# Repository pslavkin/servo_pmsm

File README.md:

# PMSM Servo motor driver based on C2000 - PCB

> development of a customized high precision microcontrolled permament magnet embedded servo motor

## Progress
<!--- 
- 
- 
- 
- 
embedded gist

https://gist.github.com/rxaviers/7360908

- :heavy_check_mark: connected to a chinise CNC works!
- :red_circle:       Dual core interconnect IPC
-->
- :heavy_check_mark:    controller schematics from Altium to kicad
- :heavy_check_mark:    setting kicad libs, datasheet, remove unused IC's
- :heavy_check_mark:    mixing high power cirtuit to kicad
- :heavy_check_mark:    two servo motor control on same board aproach!
- :heavy_check_mark:    setting kicad libs, datasheet, remove unused IC's 
- :heavy_check_mark:    adc
- :heavy_check_mark:    igbt interface
- :heavy_check_mark:    lem measurement
- :heavy_check_mark:    ac input
- :heavy_check_mark:    connect interfaces to GPIO's (ecat0/1, enet, leds, etc)
- :heavy_check_mark:    shunt using isolated ADC fron/backend
- :heavy_check_mark:    isolated GPI for external switches and sensor on any polarity
- :heavy_check_mark:    8 channel buffer to drive IGBT
- :heavy_check_mark:    ac/dc -> dc/dc -> ldo for clean power supplies
- :heavy_check_mark:        Line voltage measurement
- :heavy_check_mark:        overcurrent protection using CMPSS
- :red_circle:          aborted! lem is better changing/adding shunt measurement with sigma deltas isolated ADC
- :heavy_check_mark:    LEM revival. I've decided to return to the idea of LEM 'cose sigma
  delta carry more complexity and less benefits. But SD could be included on power stage and
I'll let pins to aquire and filter it.
- :heavy_check_mark:     schematics ready!, and check rules passed. go to part numbering and
  footprint selection
- :red_circle:          isolated GPIO aborted! I've reise free pins that comes from IGBT
- :heavy_check_mark:    EVE LCD driven choosen as the UI by spi.. I's all the thinks we need
- :heavy_check_mark:    3d added EVE LCD 3. 20w offline ac/dc changed to 10w. 15vcold
  eliminated, two buttons eliminated. 2 LEM's eliminated
- :construction:        all footprints choosen, but deserves some comprobation
- :heavy_check_mark:    placement rought done
- :heavy_check_mark:    ronting..
- :heavy_check_mark:    moving ethernet connector to right and remove 15vh->5vh and debuh
- :heavy_check_mark:    ronting DONE!!! begin to improve nets..
- :heavy_check_mark:    Gerbers READY.. leaving Moldova...
- :heavy_check_mark:    Gerbers RELOADED from Bariloche
- :heavy_check_mark:    Gerbers RELEAED ... cross fingers..
- :heavy_check_mark:    Board partially manufactured!! miss uC that is traveling on a
  boat...see pics

## Welcome back Moldova 3.0

I've come back to finish PCB, there we are... sdarobia!

## Table of Contents

- [schematics](#schematics)
- [Contributing](#contributing)
- [Team](#team)
- [FAQ](#faq)
- [Support](#support)
- [Hierarchy](#hierarchy)
- [License](#license)
---
## schematics
There are the actual schematics generated until now:

## complete pdf link
[complete pdf schematic](./doc/pics/servo.pdf)

## Layout
Met's begin with layout!
first pic, easy, doesn't it?

## A mounting optional case shape

## Nets plane 2d and 3d nets

## Video 3d rotating PCB

## schematic in pics

## Manufactured PCB

I wanna cry! 

## Hierarchy

<!-- tree --ignore-case -L 3 -I "*utils*|*user*|*target*|*Debug*|Release|include|driverlib|tags|*types_c*" -->

```ruby

```

<!--

## Features
## Usage (Optional)
## Documentation (Optional)
## Tests (Optional)

- Going into more detail on code and technologies used
- I utilized this nifty <a href="https://github.com/adam-p/markdown-here/wiki/Markdown-Cheatsheet" target="_blank">Markdown Cheatsheet</a> for this sample `README`.

## Contributing

## Team

| <a href="https://github.com/pslavkin" target="_blank">**pslavkin**</a> | <a href="https://github.com/pslavkin" target="_blank">**neo**</a> | <a href="https://github.com/pslavkin" target="_blank">**doe**</a> |
| :---: |:---:| :---:|
|     |  |   |
| <a href="https://github.com/pslavkin" target="_blank">`github.com/pslavkin`</a> | <a href="https://github.com/pslavkin" target="_blank">`github.com/pslavkin`</a> | <a href="https://github.com/pslavkin" target="_blank">`github.com/pslavkin`</a> |

## Support

Reach out to me at one of the following places!
- <a href="http://www.ti.com/tool/launchXL-F28379d#" target="_blank">**launchXL-F28379d** </a>

## License

- **[MIT license](http://opensource.org/licenses/mit-license.php)**
- Copyright 2019 © <a href="http://fvcproductions.com" target="_blank">FVCproductions</a>.

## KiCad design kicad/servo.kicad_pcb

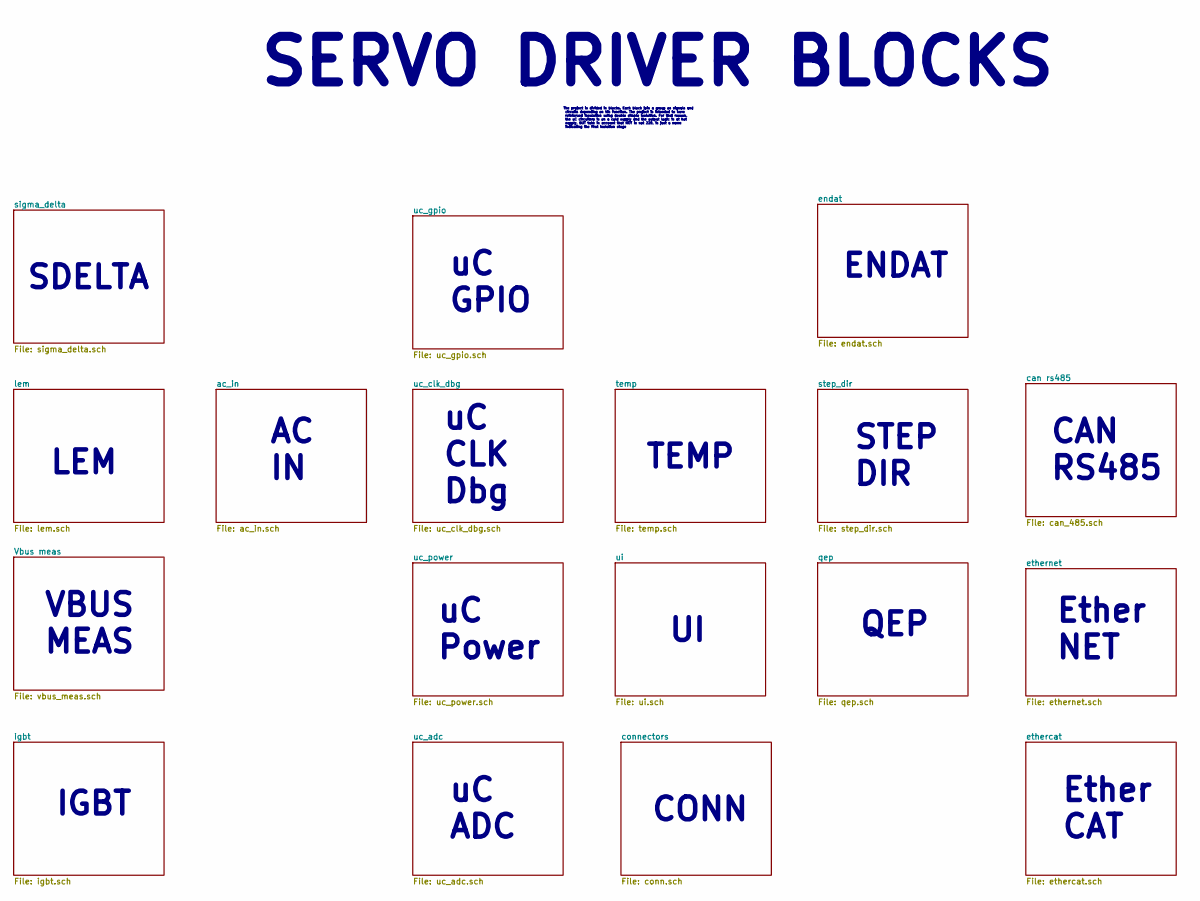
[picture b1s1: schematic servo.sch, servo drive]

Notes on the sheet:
uC ADC
IGBT
uC Power
Ether CAT
TEMP
AC IN
Ether NET
uC CLK Dbg
STEP DIR
QEP
CAN RS485
uC GPIO
LEM
VBUS MEAS
CONN
SERVO DRIVER BLOCKS
The project is divided in blocks. Each block join a group os signals and circuits depending on his function. The project is intended to have reinforced insulation using double simple isolation. For that reason, the uC circuitery is on a cold supply and the output logic is at hot supply, BUT take in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
SDELTA
ENDAT

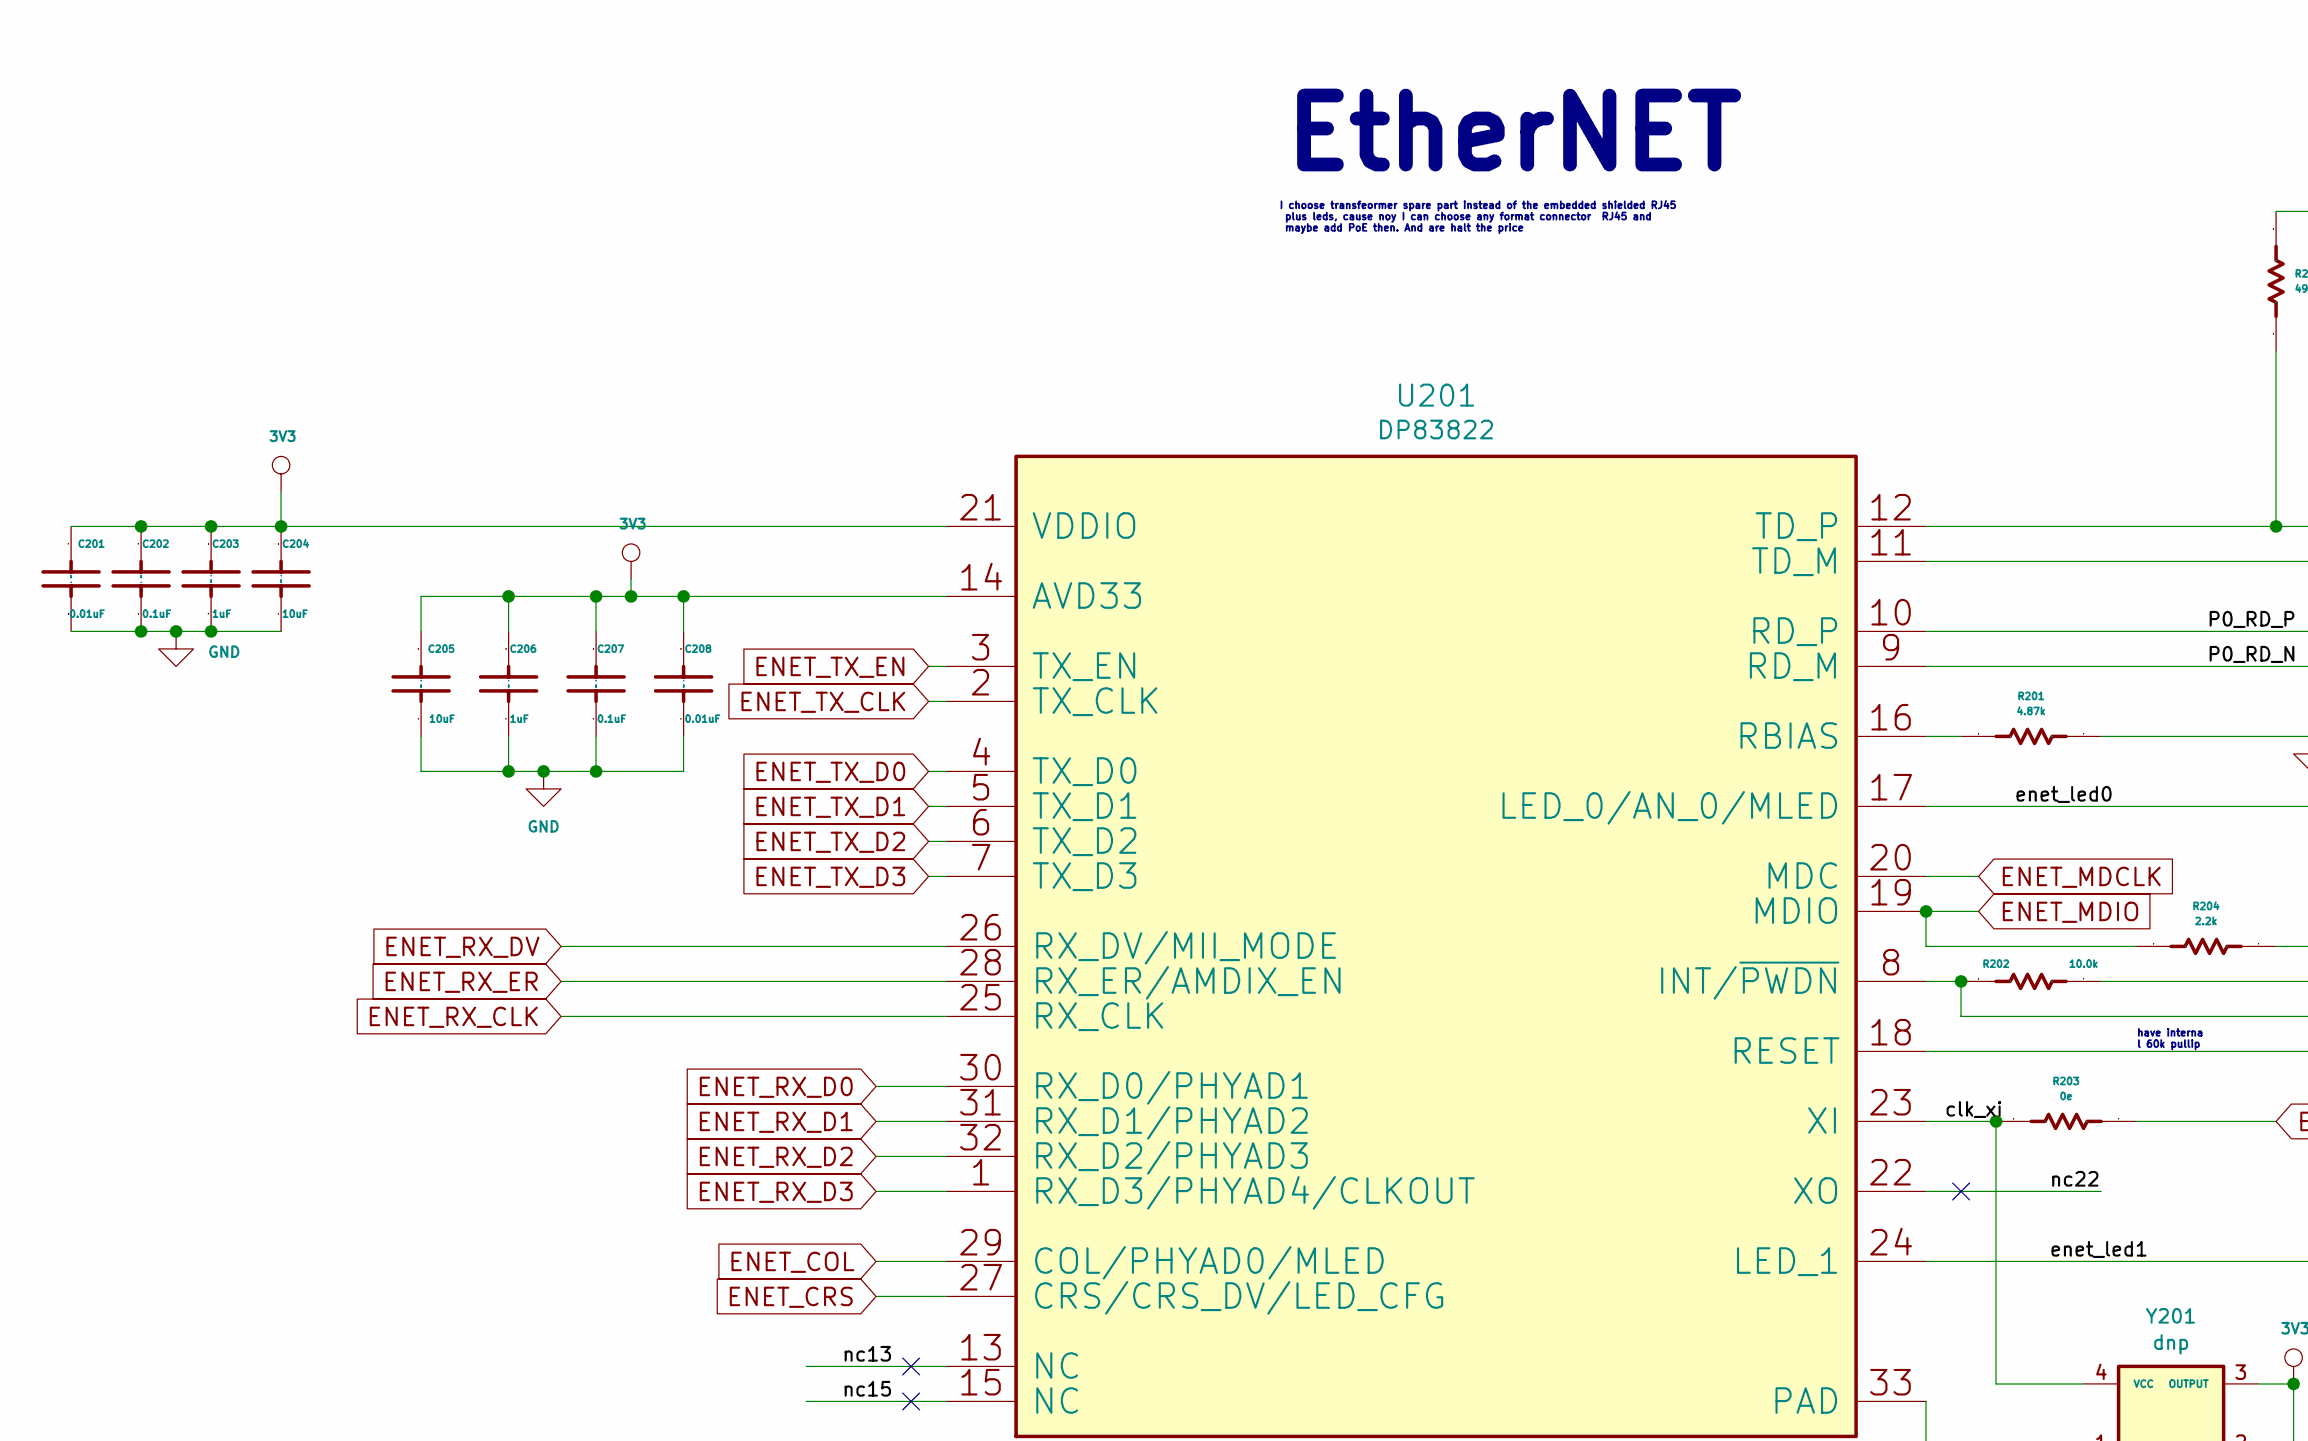
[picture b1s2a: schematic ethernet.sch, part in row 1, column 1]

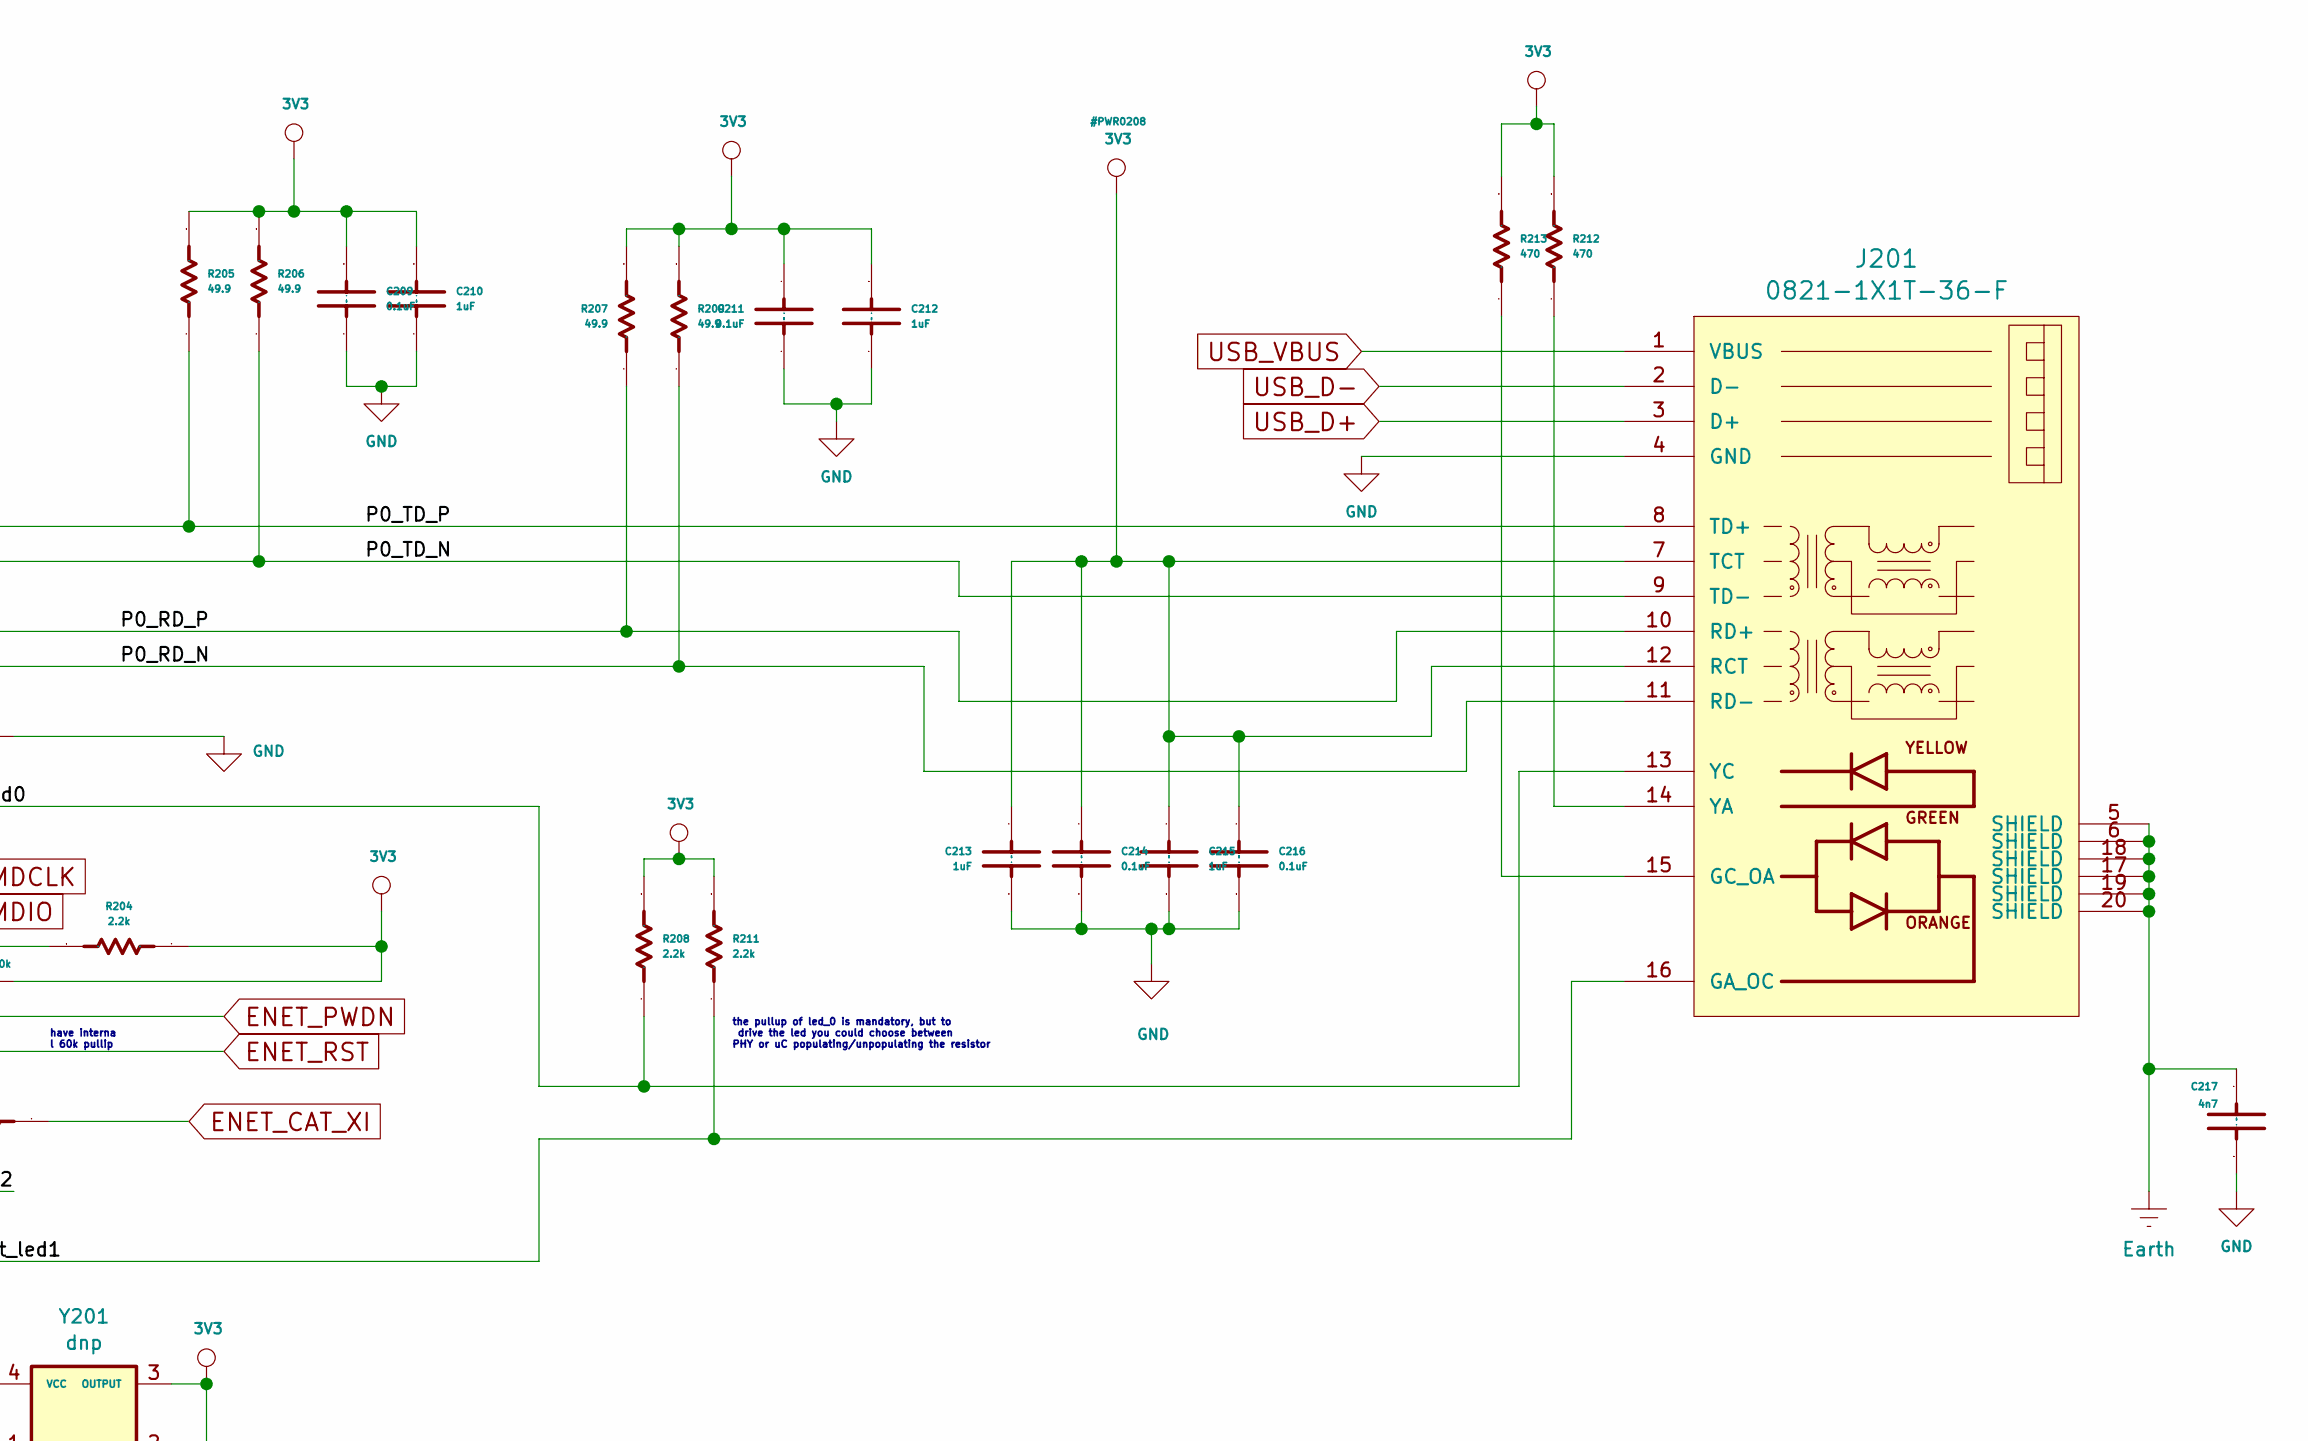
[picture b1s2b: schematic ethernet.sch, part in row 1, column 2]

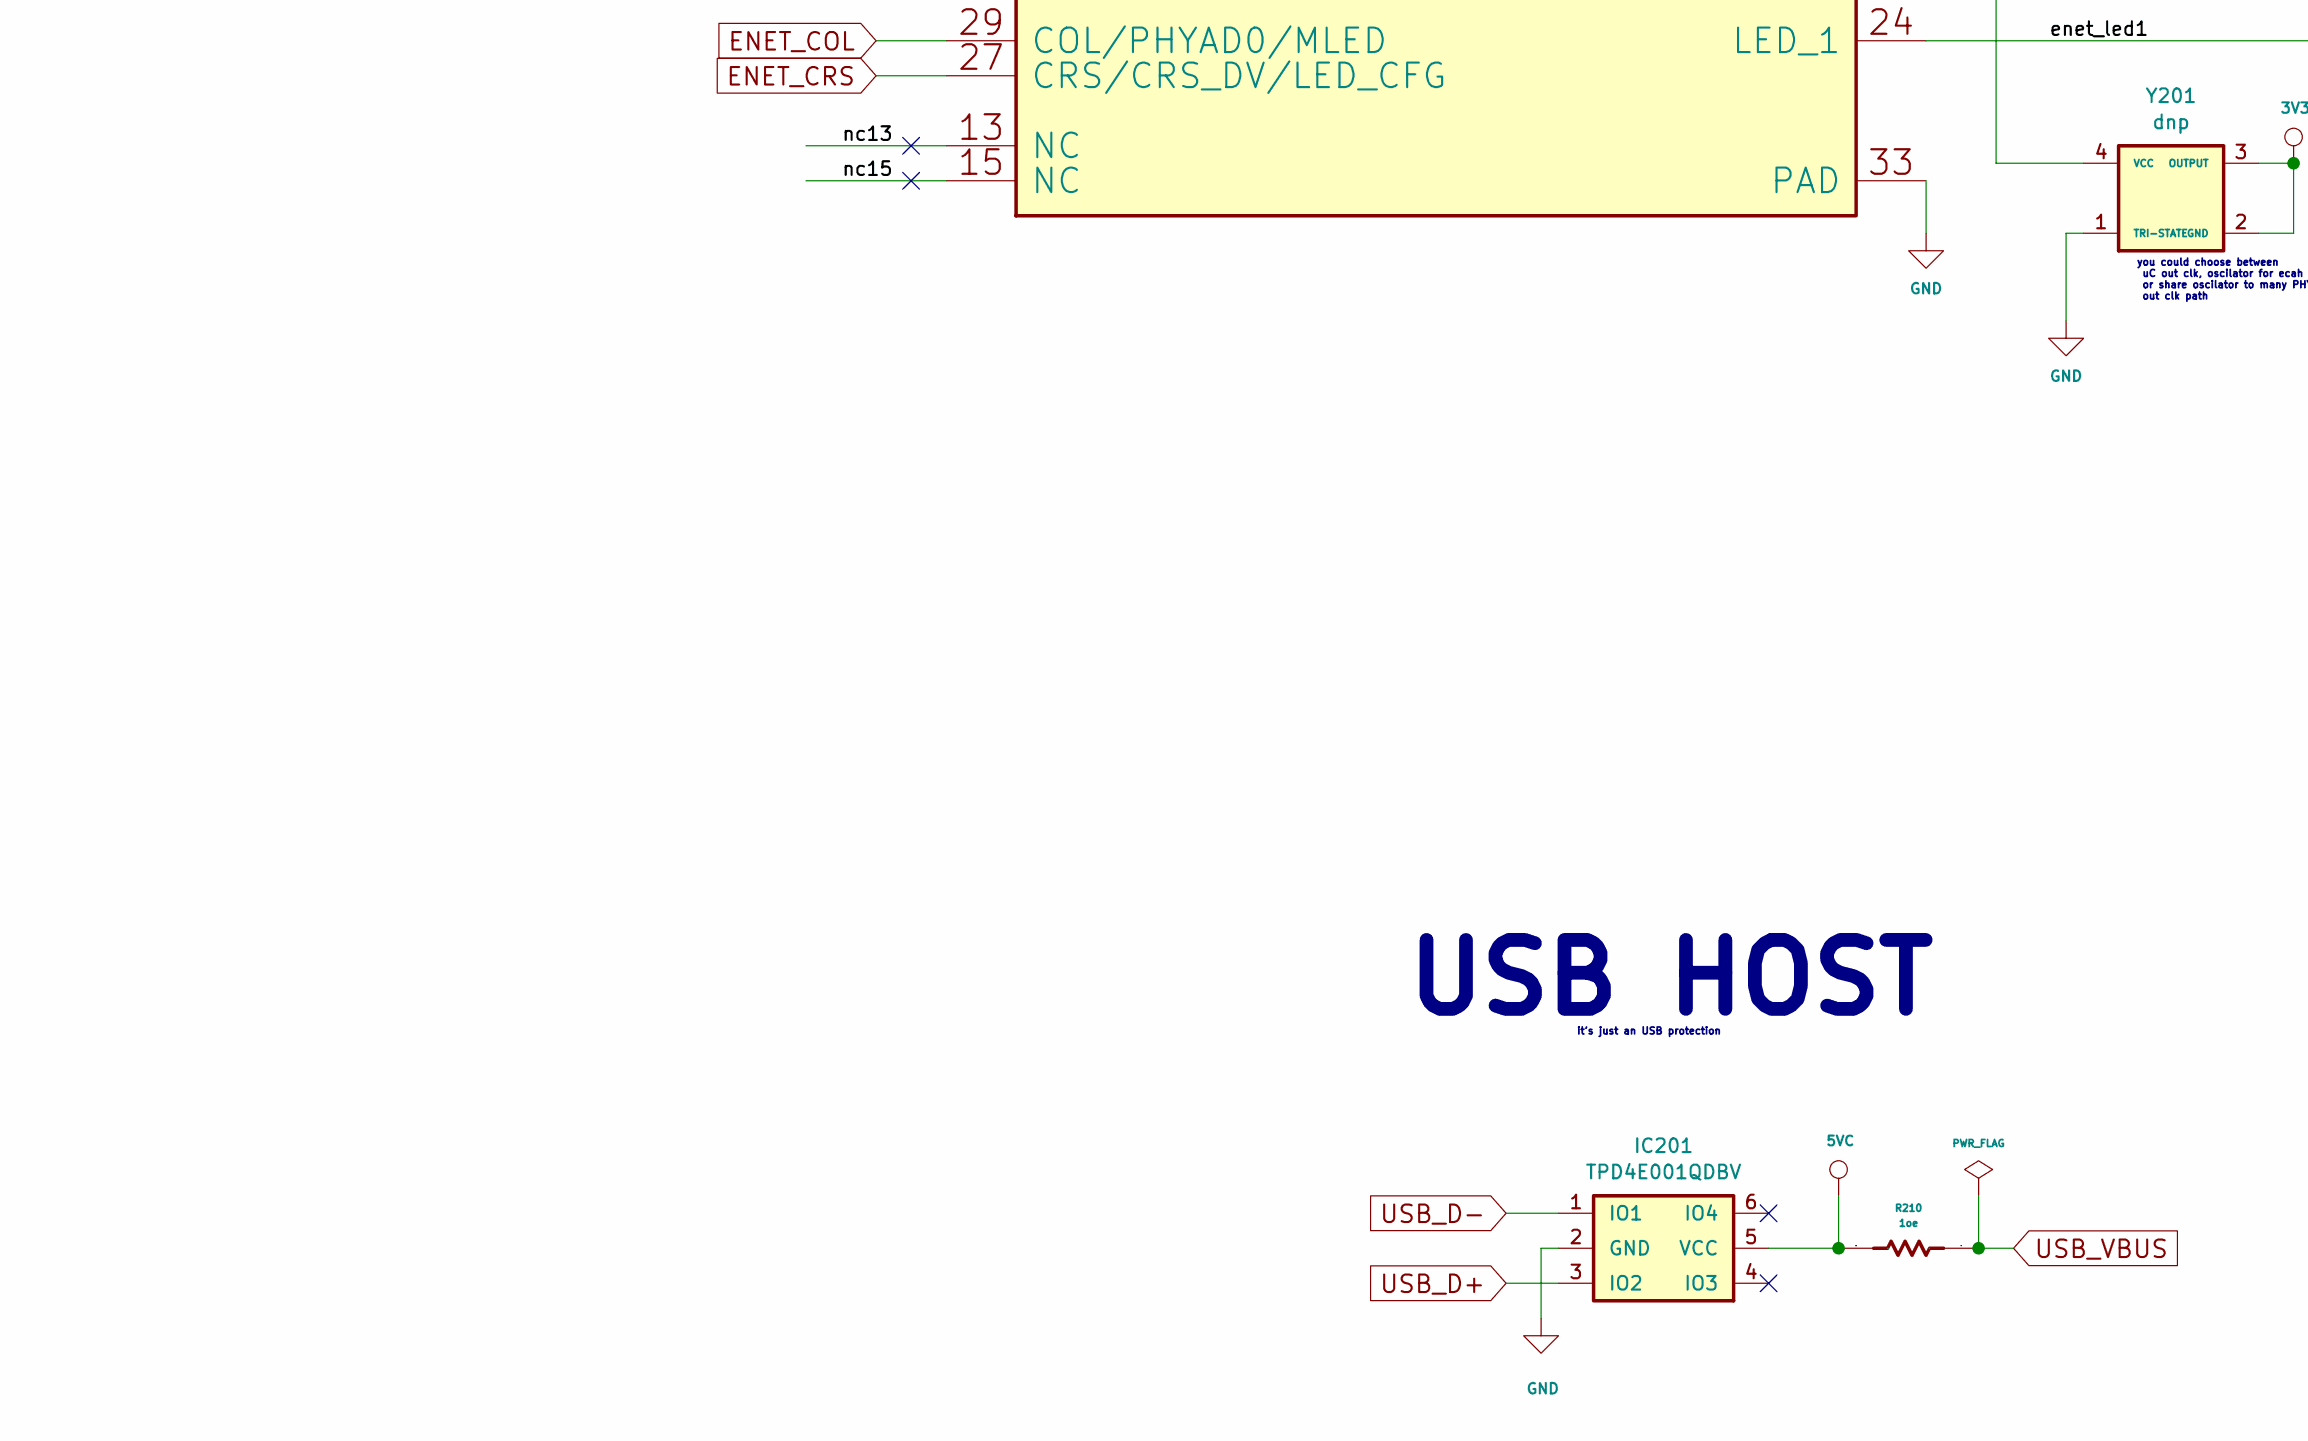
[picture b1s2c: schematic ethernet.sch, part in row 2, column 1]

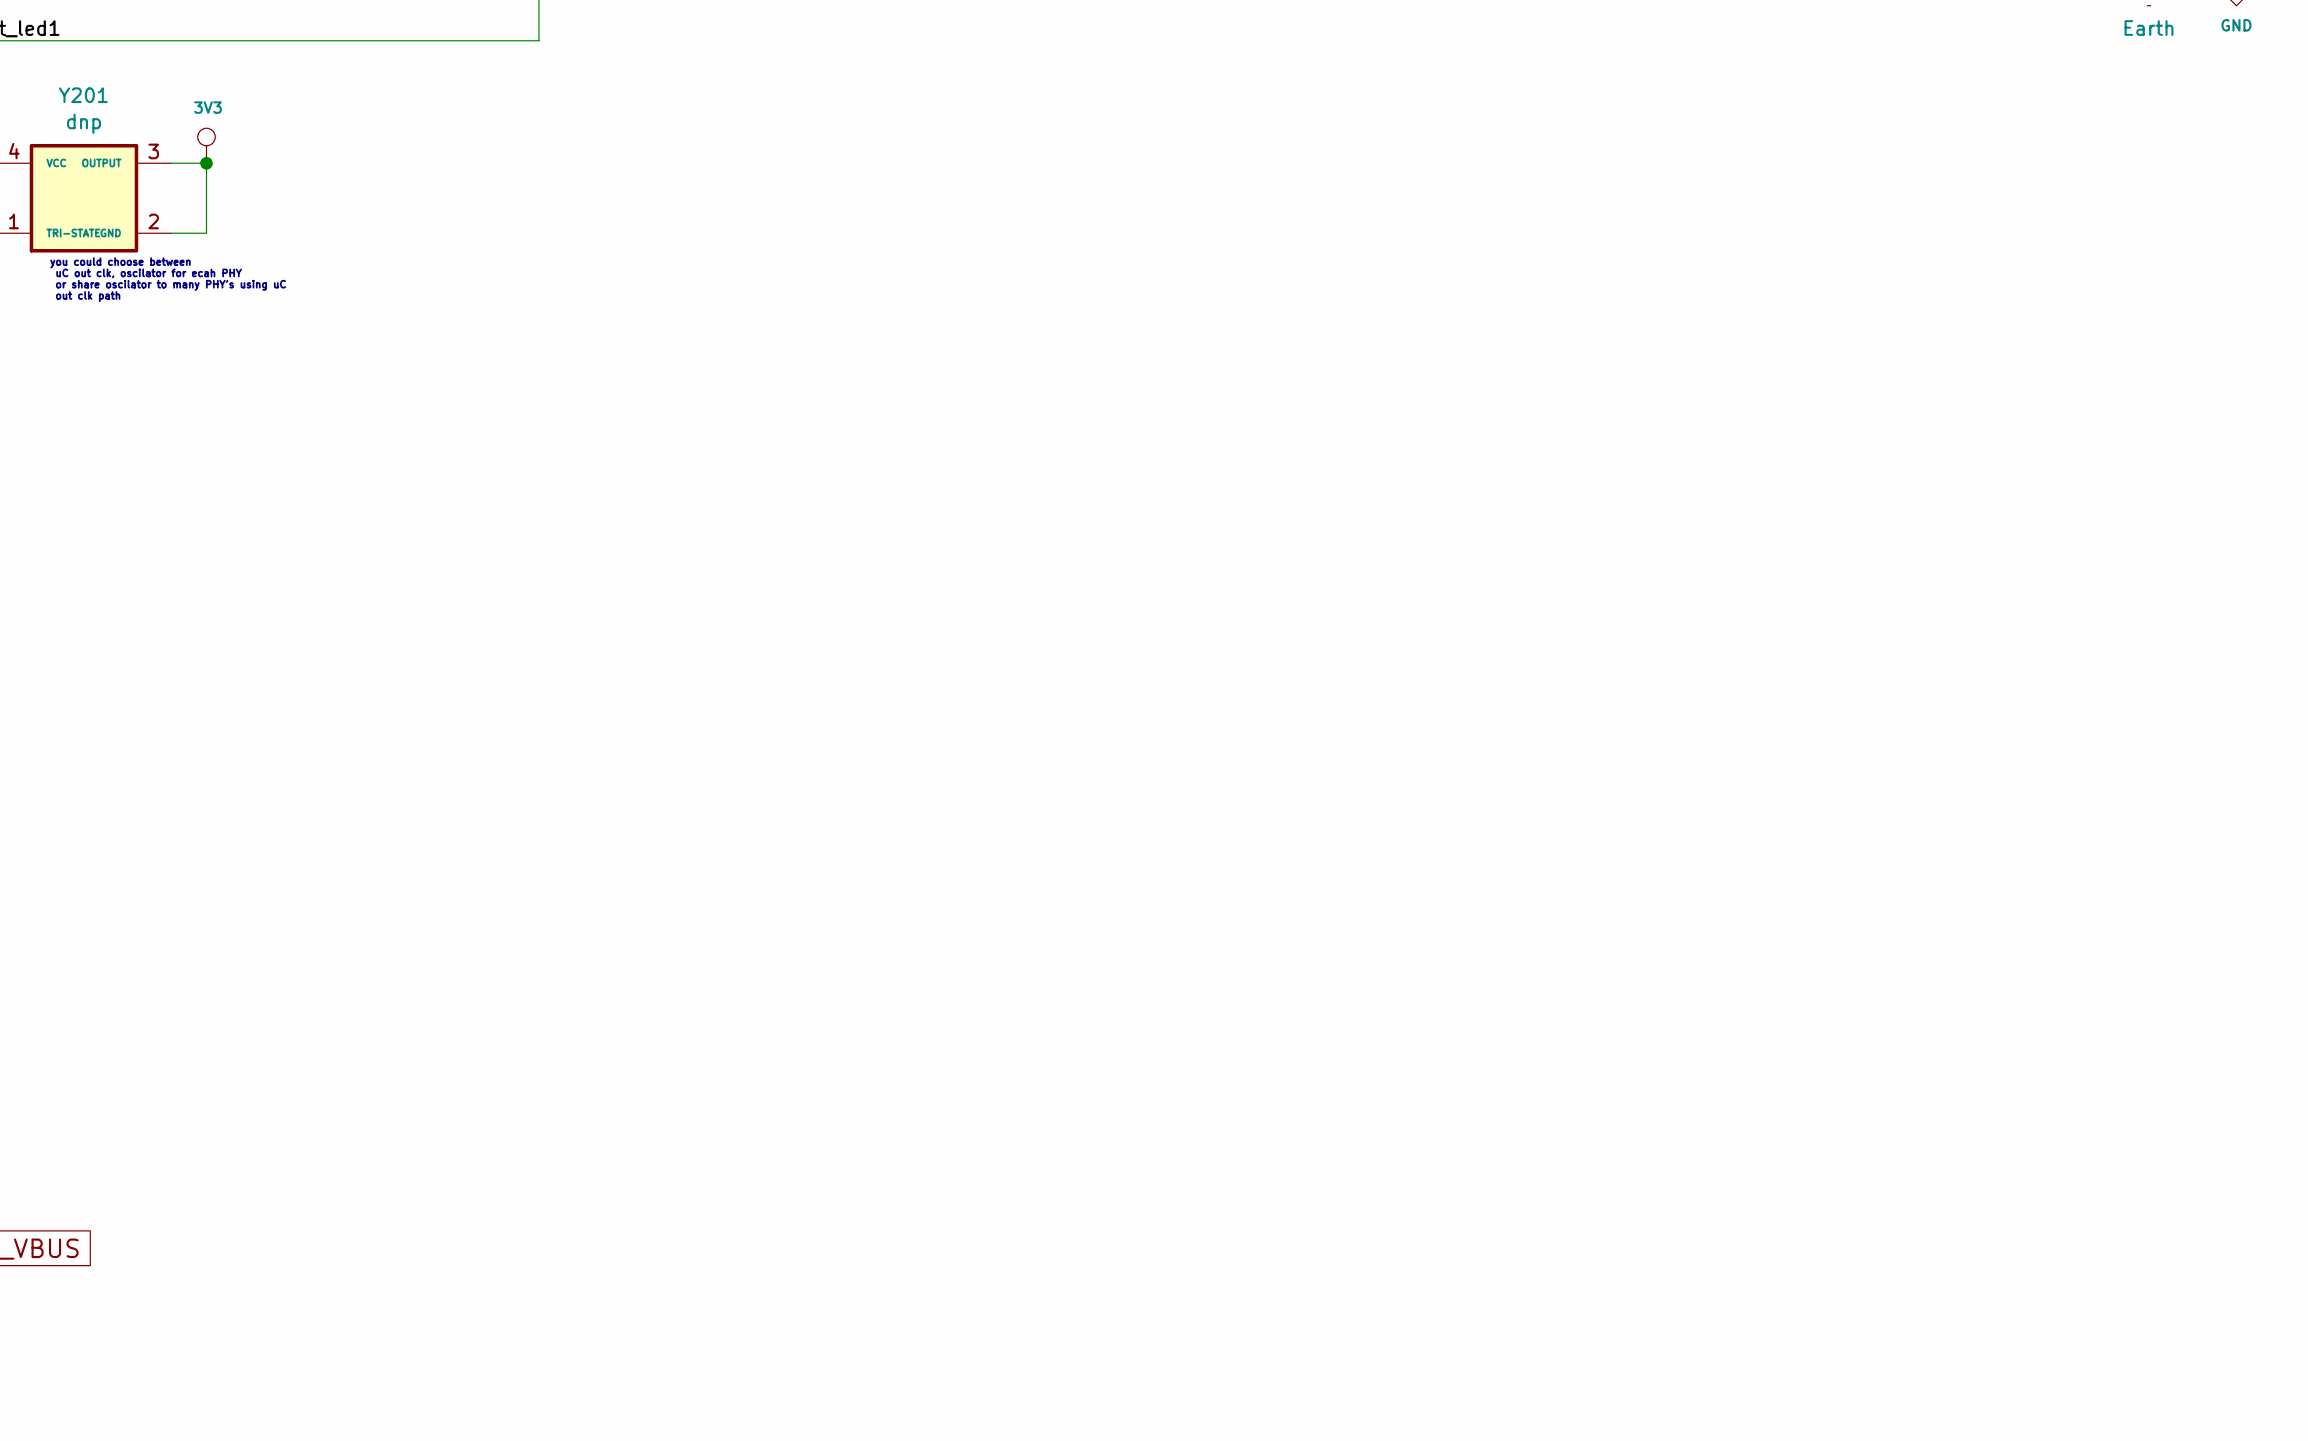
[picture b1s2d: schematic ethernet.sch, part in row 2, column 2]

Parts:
C201, C208: 0.01uF; C_0603_1608Metric
C202, C207, C209, C211, C214, C216: 0.1uF; C_0603_1608Metric
C203, C206, C210, C212, C213, C215: 1uF; C_0603_1608Metric
C204, C205: 10uF; C_0603_1608Metric
C217: 4n7; C_1206_3216Metric
IC201: TPD4E001QDBV; SOT-23-6
J201: 0821-1X1T-36-F; BEL_0821-1X1T-36-F
R201: 4.87k; R_0603_1608Metric
R202: 10.0k; R_0603_1608Metric
R203: 0e; R_0603_1608Metric
R204, R208, R211: 2.2k; R_0603_1608Metric
R205, R206, R207, R209: 49.9; R_0603_1608Metric
R210: 1oe; R_1206_3216Metric_Pad1.42x1.75mm_HandSolder
R212, R213: 470; R_0603_1608Metric
U201: DP83822; QFN-32-1EP_5x5mm_P0.5mm_EP2.9x2.9mm_ThermalVias; PartNumber DP83822IRHBR
Y201: dnp; Oscillator_SMD_SeikoEpson_SG210-4Pin_2.5x2.0mm

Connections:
3V3: C201.2 (Capacitor), C202.2 (Capacitor), C203.1, C204.1, C205.1, C206.1, C207.1, C208.1, C209.1, C210.1, C211.1, C212.1, C213.2 (Capacitor), C214.2 (Capacitor), C215.2 (Capacitor), C216.2 (Capacitor), J201.7 (TCT), J201.12 (RCT), R202.2, R204.2, R205.1, R206.1, R207.1, R208.1, R209.1, R211.1, R212.1, R213.1, U201.14 (AVD33), U201.21 (VDDIO), Y201.2 (GND), Y201.3 (OUTPUT); also elsewhere on the board
5VC: IC201.5 (VCC), R210.1; also elsewhere on the board
/ethernet/P0_RD_N: J201.11 (RD-), R209.2, U201.9 (RD_M)
/ethernet/P0_RD_P: J201.10 (RD+), R207.2, U201.10 (RD_P)
/ethernet/P0_TD_N: J201.9 (TD-), R206.2, U201.11 (TD_M)
/ethernet/P0_TD_P: J201.8 (TD+), R205.2, U201.12 (TD_P)
/ethernet/clk_xi: R203.1, U201.23 (XI), Y201.4 (VCC)
/ethernet/enet_led0: J201.13 (YC), R208.2, U201.17 (LED_0/AN_0/MLED)
/ethernet/enet_led1: J201.16 (GA_OC), R211.2, U201.24 (LED_1)
/ethernet/nc13: U201.13 (NC)
/ethernet/nc15: U201.15 (NC)
/ethernet/nc22: U201.22 (XO)
ENET_CAT_XI: R203.2; also elsewhere on the board
ENET_COL: U201.29 (COL/PHYAD0/MLED); also elsewhere on the board
ENET_CRS: U201.27 (CRS/CRS_DV/LED_CFG); also elsewhere on the board
ENET_MDCLK: U201.20 (MDC); also elsewhere on the board
ENET_MDIO: R204.1, U201.19 (MDIO); also elsewhere on the board
ENET_PWDN: R202.1, U201.8 (INT/~PWDN); also elsewhere on the board
ENET_RST: U201.18 (RESET); also elsewhere on the board
ENET_RX_CLK: U201.25 (RX_CLK); also elsewhere on the board
ENET_RX_D0: U201.30 (RX_D0/PHYAD1); also elsewhere on the board
ENET_RX_D1: U201.31 (RX_D1/PHYAD2); also elsewhere on the board
ENET_RX_D2: U201.32 (RX_D2/PHYAD3); also elsewhere on the board
ENET_RX_D3: U201.1 (RX_D3/PHYAD4/CLKOUT); also elsewhere on the board
ENET_RX_DV: U201.26 (RX_DV/MII_MODE); also elsewhere on the board
ENET_RX_ER: U201.28 (RX_ER/AMDIX_EN); also elsewhere on the board
ENET_TX_CLK: U201.2 (TX_CLK); also elsewhere on the board
ENET_TX_D0: U201.4 (TX_D0); also elsewhere on the board
ENET_TX_D1: U201.5 (TX_D1); also elsewhere on the board
ENET_TX_D2: U201.6 (TX_D2); also elsewhere on the board
ENET_TX_D3: U201.7 (TX_D3); also elsewhere on the board
ENET_TX_EN: U201.3 (TX_EN); also elsewhere on the board
Earth: C217.2 (Capacitor), J201.5 (SHIELD), J201.6 (SHIELD), J201.17 (SHIELD), J201.18 (SHIELD), J201.19 (SHIELD), J201.20 (SHIELD); also elsewhere on the board
GND: C201.1, C202.1, C203.2 (Capacitor), C204.2 (Capacitor), C205.2 (Capacitor), C206.2 (Capacitor), C207.2 (Capacitor), C208.2 (Capacitor), C209.2 (Capacitor), C210.2 (Capacitor), C211.2 (Capacitor), C212.2 (Capacitor), C213.1, C214.1, C215.1, C216.1, C217.1, IC201.2 (GND), J201.4 (GND), R201.2, U201.33 (PAD), Y201.1 (TRI-STATE); also elsewhere on the board
unnamed: J201.14 (YA), R212.2
unnamed: J201.15 (GC_OA), R213.2
unnamed: R201.1, U201.16 (RBIAS)
USB_D+: IC201.3 (IO2), J201.3 (D+); also elsewhere on the board
USB_D-: IC201.1 (IO1), J201.2 (D-); also elsewhere on the board
USB_VBUS: J201.1 (VBUS), R210.2

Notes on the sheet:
EtherNET
you could choose between uC out clk, oscilator for ecah PHY or share oscilator to many PHY's using uC out clk path
the pullup of led_0 is mandatory, but to drive the led you could choose between PHY or uC populating/unpopulating the resistor
I choose transfeormer spare part instead of the embedded shielded RJ45 plus leds, cause noy I can choose any format connector RJ45 and maybe add PoE then. And are halt the price
USB HOST
it's just an USB protection
have interna l 60k pullip

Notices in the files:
common/source/F2837xD_Mcbsp.c:
Copyright (C) 2013-2019 Texas Instruments Incorporated - http://www.ti.com
